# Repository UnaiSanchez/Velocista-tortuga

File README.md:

# RobotVelocista
Robot velocista
  Es un robot velocista con una tortuga kawaii

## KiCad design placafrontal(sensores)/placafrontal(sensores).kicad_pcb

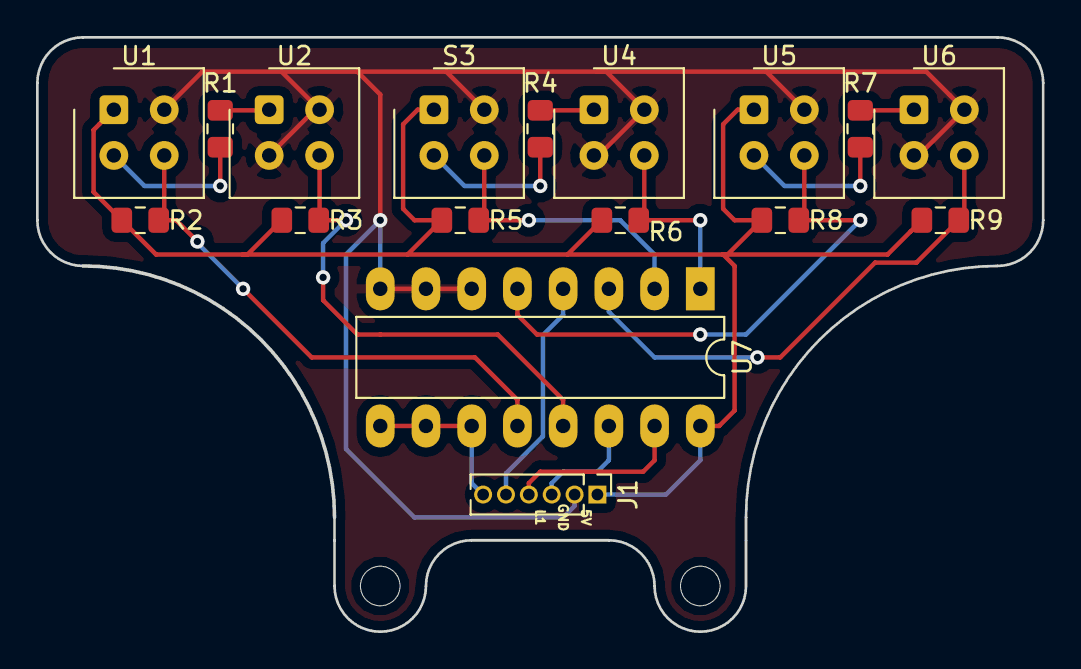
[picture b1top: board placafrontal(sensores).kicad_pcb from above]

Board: 2 copper layers, 55.9 x 33.0 mm, 17 parts (0 on the bottom side), 18 nets.

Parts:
J1: Conector; PinHeader_1x06_P1.27mm_Vertical
R1, R4, R7: 82; R_0805_2012Metric_Pad1.15x1.40mm_HandSolder
R2, R3, R5, R6, R8, R9: 10k; R_0805_2012Metric_Pad1.15x1.40mm_HandSolder
S3: CNY70; Vishay_CNY70
U1, U2, U4, U5, U6: CNY70; Vishay_CNY70
U7: 4053; DIP-16_W7.62mm_LongPads

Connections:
+5V: J1.1, R2.1, R3.1, R5.1, R6.1, R8.1, R9.1, S3.1, U1.1, U5.1, U7.16
/linea1: J1.3, U7.14
/linea2: J1.4, U7.15
/linea3: J1.5, U7.4
/linea_selec: J1.6, U7.9, U7.10, U7.11
/sensor1: R2.2, U1.3, U7.12
/sensor2: R3.2, U2.3, U7.13
/sensor3: R5.2, S3.3, U7.2
/sensor4: R6.2, U4.3, U7.1
/sensor5: R8.2, U5.3, U7.5
/sensor6: R9.2, U6.3, U7.3
GND: J1.2, S3.4, U1.4, U2.2, U2.4, U4.2, U4.4, U5.4, U6.2, U6.4, U7.6, U7.7, U7.8
unnamed: R1.1, U1.2
unnamed: R1.2, U2.1
unnamed: R4.1, S3.2
unnamed: R4.2, U4.1
unnamed: R7.1, U5.2
unnamed: R7.2, U6.1

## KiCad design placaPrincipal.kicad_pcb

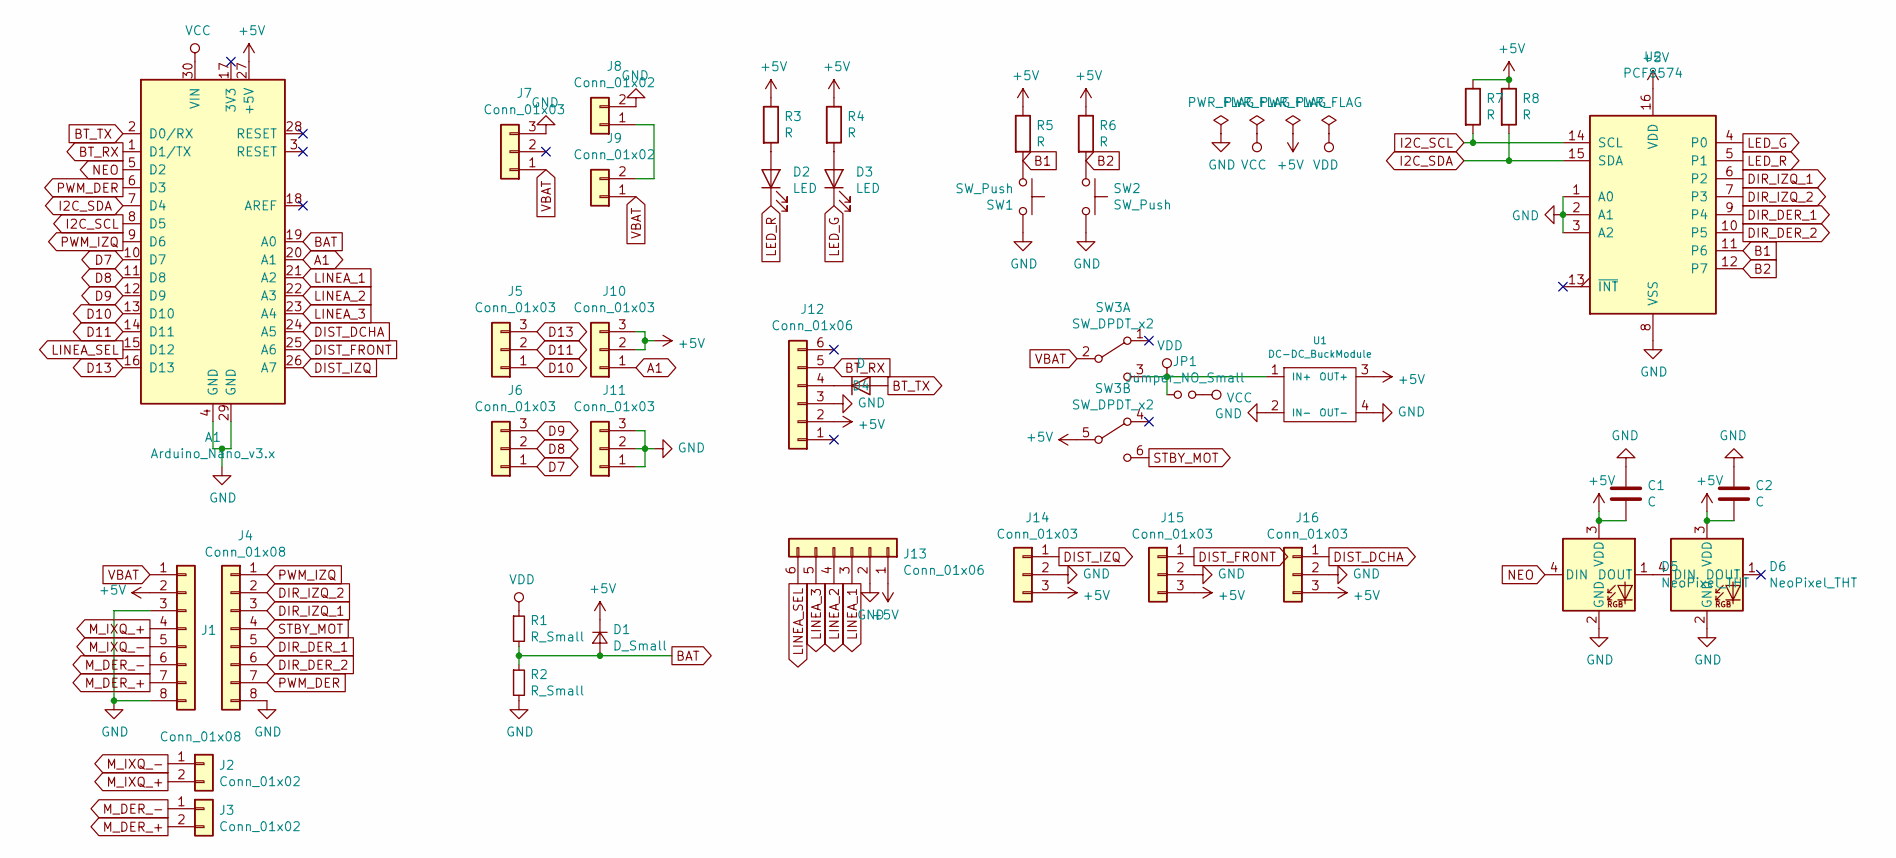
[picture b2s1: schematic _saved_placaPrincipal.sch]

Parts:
A1: Arduino_Nano_v3.x; Arduino_Nano
C1, C2: C; C_0805_2012Metric_Pad1.15x1.40mm_HandSolder
D1: D_Small; D_DO-41_SOD81_P7.62mm_Horizontal
D2, D3: LED; LED_D3.0mm
D4: D; D_DO-41_SOD81_P7.62mm_Horizontal
D5, D6: NeoPixel_THT; LED_D5.0mm-4_RGB
J1, J4: Conn_01x08; PinSocket_1x08_P2.54mm_Vertical
J2, J3: Conn_01x02; PinSocket_1x02_P2.54mm_Vertical
J5, J6, J10, J11, J14, J15, J16: Conn_01x03; PinSocket_1x03_P2.54mm_Vertical
J7: Conn_01x03; JST_XH_B03B-XH-A_1x03_P2.50mm_Vertical
J8, J9: Conn_01x02; JST_PH_B2B-PH-K_1x02_P2.00mm_Vertical
J12, J13: Conn_01x06; PinSocket_1x06_P2.54mm_Vertical
JP1: Jumper_NO_Small; SolderJumper-2_P1.3mm_Open_RoundedPad1.0x1.5mm
R1, R2: R_Small; R_0805_2012Metric_Pad1.15x1.40mm_HandSolder
R3, R4, R5, R6, R7, R8: R; R_0805_2012Metric_Pad1.15x1.40mm_HandSolder
SW1, SW2: SW_Push; SW_PUSH_6mm
SW3: SW_DPDT_x2; SW_CuK_JS202011CQN_DPDT_Straight
U1: DC-DC_BuckModule; DC-DC-MP2307
U2: PCF8574; DIP-16_W7.62mm_LongPads

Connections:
+5V: A1.27 (+5V), C1.2, C2.2, D1.1 (K), D5.3 (VDD), D6.3 (VDD), J1.2, J10.2, J10.3, J12.2, J13.1, J14.3, J15.3, J16.3, R3.1, R4.1, R5.1, R6.1, R7.1, R8.1, SW3.5 (B), U1.3 (OUT+), U2.16 (VDD)
A1: A1.20 (A1), J10.1
B1: R5.2, SW1.1, U2.11 (P6)
B2: R6.2, SW2.1, U2.12 (P7)
BAT: A1.19 (A0), D1.2 (A), R1.2, R2.1
BT_RX: A1.1 (D1/TX), J12.5
BT_TX: A1.2 (D0/RX), D4.2 (A)
D7: A1.10 (D7), J6.1
D8: A1.11 (D8), J6.2
D9: A1.12 (D9), J6.3
D10: A1.13 (D10), J5.1
D11: A1.14 (D11), J5.2
D13: A1.16 (D13), J5.3
DIR_DER_1: J4.5, U2.9 (P4)
DIR_DER_2: J4.6, U2.10 (P5)
DIR_IZQ_1: J4.3, U2.6 (P2)
DIR_IZQ_2: J4.2, U2.7 (P3)
DIST_DCHA: A1.24 (A5), J16.1
DIST_FRONT: A1.25 (A6), J15.1
DIST_IZQ: A1.26 (A7), J14.1
GND: A1.4 (GND), A1.29 (GND), C1.1, C2.1, D5.2 (GND), D6.2 (GND), J1.3, J1.8, J4.8, J7.3, J8.2, J11.1, J11.2, J11.3, J12.3, J13.2, J14.2, J15.2, J16.2, R2.2, SW1.2, SW2.2, U1.2 (IN-), U1.4 (OUT-), U2.1 (A0), U2.2 (A1), U2.3 (A2), U2.8 (VSS)
I2C_SCL: A1.8 (D5), R7.2, U2.14 (SCL)
I2C_SDA: A1.7 (D4), R8.2, U2.15 (SDA)
LED_G: D3.1 (K), U2.4 (P0)
LED_R: D2.1 (K), U2.5 (P1)
LINEA_1: A1.21 (A2), J13.3
LINEA_2: A1.22 (A3), J13.4
LINEA_3: A1.23 (A4), J13.5
LINEA_SEL: A1.15 (D12), J13.6
M_DER_+: J1.7, J3.2
M_DER_-: J1.6, J3.1
M_IXQ_+: J1.4, J2.2
M_IXQ_-: J1.5, J2.1
NEO: A1.5 (D2), D5.4 (DIN)
unnamed: D2.2 (A), R3.2
unnamed: D3.2 (A), R4.2
unnamed: D4.1 (K), J12.4
unnamed: D5.1 (DOUT), D6.4 (DIN)
unnamed: J8.1, J9.2
PWM_DER: A1.6 (D3), J4.7
PWM_IZQ: A1.9 (D6), J4.1
STBY_MOT: J4.4, SW3.6 (C)
VBAT: J1.1, J7.1, J9.1, SW3.2 (B)
VCC: A1.30 (VIN), JP1.2
VDD: JP1.1, R1.1, SW3.3 (C), U1.1 (IN+)

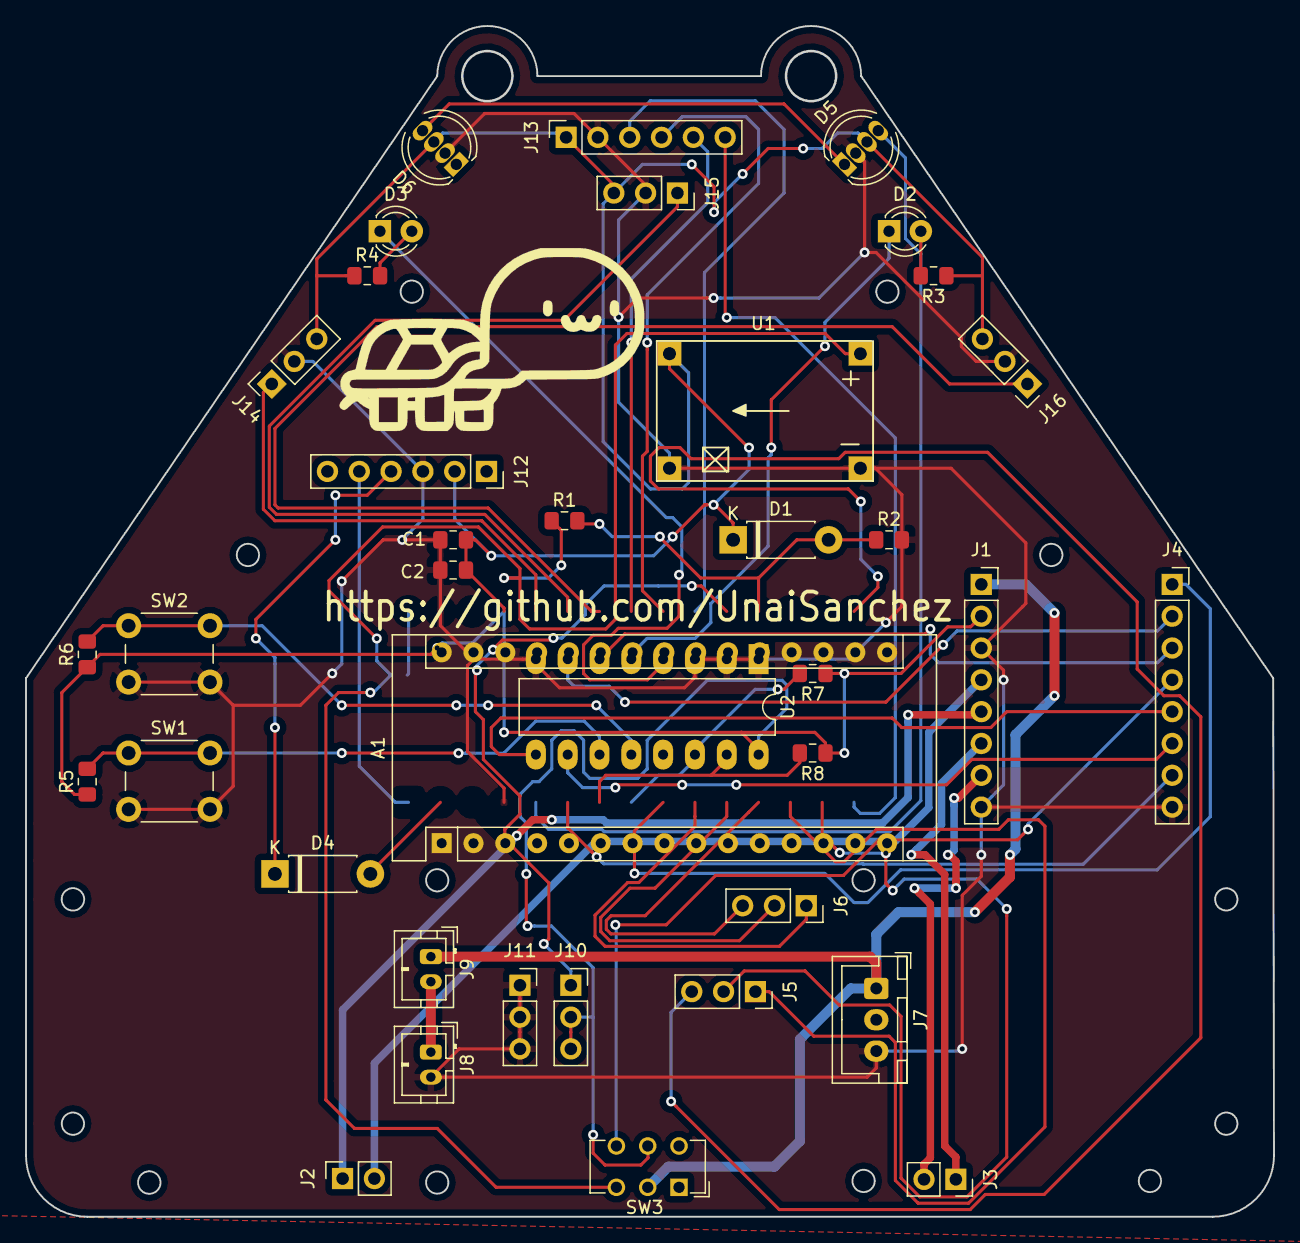
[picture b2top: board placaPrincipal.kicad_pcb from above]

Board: 2 copper layers, 99.6 x 95.1 mm, 39 parts (1 on the bottom side), 45 nets.

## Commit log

2019-01-26 Add files via upload
    El cuerpo de nuestro robot
